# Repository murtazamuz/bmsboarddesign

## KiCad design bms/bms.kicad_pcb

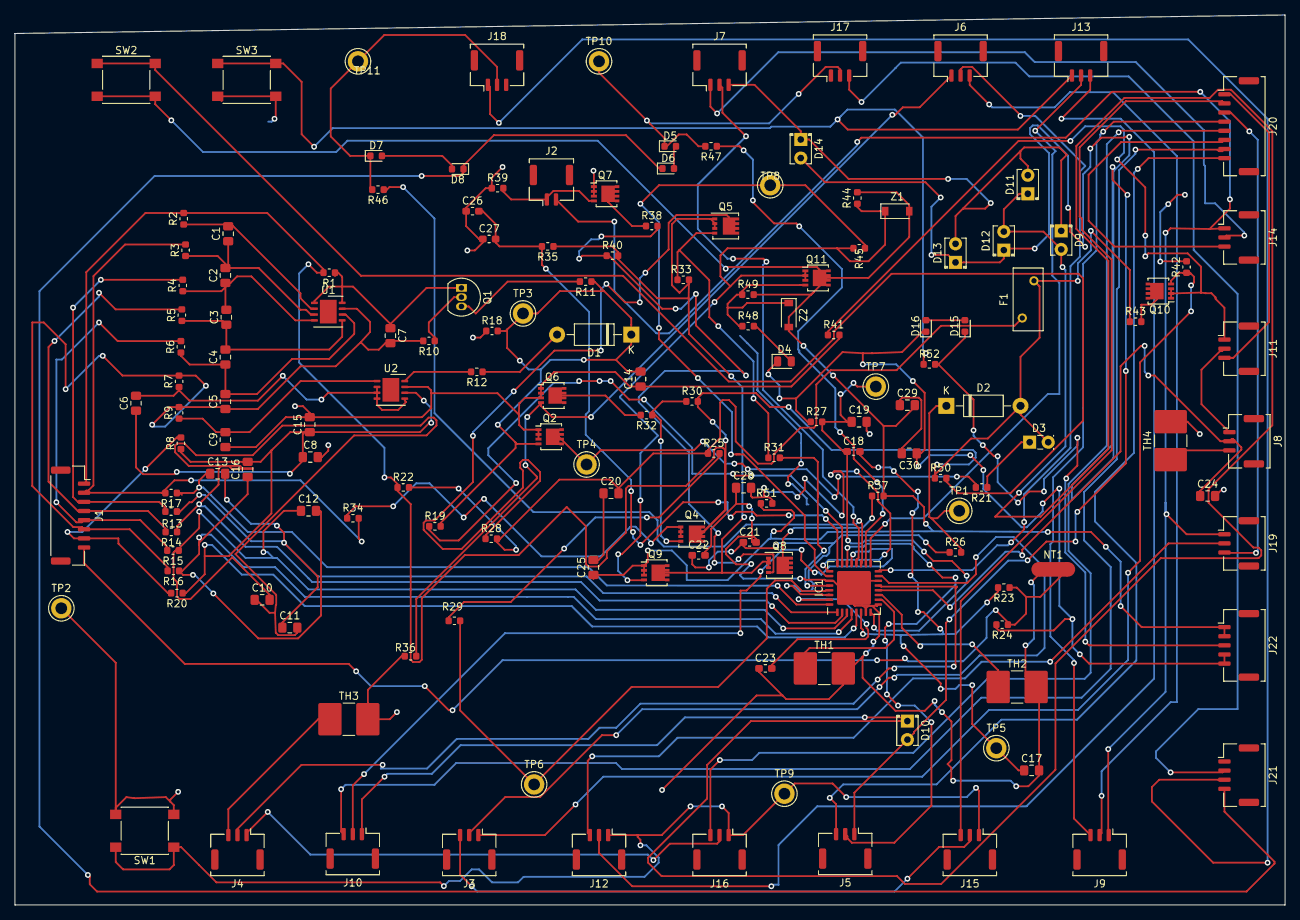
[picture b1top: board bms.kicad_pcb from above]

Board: 2 copper layers, 174.0 x 121.9 mm, 155 parts (0 on the bottom side), 109 nets.

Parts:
C1, C2, C3, C4, C5, C6, C7, C8, C9, C10, C11, C12, C13, C14, C15, C16, C17, C19, C20, C24, C25, C28, C29, C30: 0.1uF; C_0805_2012Metric_Pad1.15x1.40mm_HandSolder
C18, C21, C22, C23, C26, C27: 100pF; C_0603_1608Metric_Pad1.05x0.95mm_HandSolder
D1, D2: 1N5819; D_DO-41_SOD81_P10.16mm_Horizontal
D3: LED; LED_Rectangular_W3.9mm_H1.8mm_FlatTop
D4: DIODE; D_0805_2012Metric
D5, D6, D7, D8, D15, D16: D_Zener_ALT; D_0603_1608Metric
D9, D10, D11, D12, D13, D14: GREEN; LED_D2.0mm_W4.0mm_H2.8mm_FlatTop
F1: 30A fuse; Fuse_BelFuse_0ZRE0008FF_L8.3mm_W3.8mm
IC1: BQ40Z80RSMT; QFN-32-1EP_7x7mm_P0.65mm_EP4.65x4.65mm
J1: Conn_01x08; Molex_CLIK-Mate_502386-0870_1x08-1MP_P1.25mm_Horizontal
J2: Conn_01x02; Molex_CLIK-Mate_502382-0270_1x02-1MP_P1.25mm_Vertical
J3, J4, J5, J6, J7, J8, J9, J10, J11, J12, J13, J14, J15, J16, J17, J18, J19: Conn_01x03; Molex_CLIK-Mate_502382-0370_1x03-1MP_P1.25mm_Vertical
J20: Conn_01x08; Molex_CLIK-Mate_502382-0870_1x08-1MP_P1.25mm_Vertical
J21: Conn_01x04; Molex_CLIK-Mate_502382-0470_1x04-1MP_P1.25mm_Vertical
J22: Conn_01x05; Molex_CLIK-Mate_502382-0570_1x05-1MP_P1.25mm_Vertical
NT1: Net-Tie_2; NetTie-2_SMD_Pad2.0mm
Q1: 2N3905; TO-92_Inline
Q2: BUK7M9R9-60EX; LFPAK33
Q4, Q5, Q8: DMP3013SFV; Diodes_PowerDI3333-8
Q6, Q7, Q9, Q10, Q11: BUK7M12-40EX; LFPAK33
R1, R13, R14, R15, R16, R17, R20, R23, R26, R27, R28, R37, R46, R47: 100; R_0603_1608Metric
R2, R3, R4, R5, R6, R7, R8, R9, R10, R29, R52: 1k; R_0603_1608Metric
R11, R12, R19: 5.1k; R_0603_1608Metric
R18: 20k; R_0603_1608Metric
R21: 1K; R_0603_1608Metric
R22: 0; R_0603_1608Metric
R24: 0.001; R_0603_1608Metric
R25, R30, R32, R33, R36, R38, R39, R40, R42, R44, R48, R49: 10M; R_0603_1608Metric
R31, R50: 10k; R_0603_1608Metric
R34: 200; R_0603_1608Metric
R35: 510; R_0603_1608Metric
R41: 10K; R_0603_1608Metric
R43: 332K; R_0603_1608Metric
R45: 4.02K; R_0603_1608Metric
R51: 1.1k; R_0603_1608Metric
SW1, SW2, SW3: SW_Push_Dual; SW_Push_1P1T_NO_6x6mm_H9.5mm
TH1, TH2, TH3, TH4: Thermistor; R_2816_7142Metric_Pad3.20x4.45mm_HandSolder
TP1, TP2, TP3, TP4, TP5, TP6, TP7, TP8, TP9, TP10, TP11: TestPoint; TestPoint_Keystone_5005-5009_Compact
U1, U2: BQ771807DPJR; DFN-8-1EP_4x4mm_P0.8mm_EP2.3x3.24mm
Z1, Z2: MMSZ5246B-7-F; D_SOD-123

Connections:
6P: J1.2, R3.2, R17.2, R34.2
7P: D2.2, D3.2, F1.2, J1.1, Q4.5, R1.2, R2.2, R22.1, R30.2, R43.1, R50.1
/PACK: C28.2, IC1.25, R51.2
GNDPWR: C30.1, D4.1, D16.1, J22.4, J22.5, R24.2, R27.1
unnamed: C1.1, C2.2, R3.1, U1.3
unnamed: C1.2, R2.1, U1.2
unnamed: C2.1, C3.2, R4.1, U1.4
unnamed: C3.1, C4.2, R5.1, U1.5
unnamed: C4.1, C5.2, R6.1, U1.6
unnamed: C5.1, C7.2, J1.6, R7.2, R9.2, R10.2, R16.2, U1.7
unnamed: C6.2, R7.1, U2.2, U2.3, U2.4, U2.5
unnamed: C7.1, Q1.1, R1.1, U1.1, U1.8
unnamed: C9.2, R9.1, U2.1
unnamed: C10.1, C11.2, IC1.2, R14.1
unnamed: C10.2, C12.1, IC1.3, R15.1
unnamed: C11.1, C13.2, IC1.1, R13.1
unnamed: C12.2, C16.1, IC1.4, R16.1
unnamed: C13.1, IC1.32, R17.1
unnamed: C14.2, D1.1, Q2.4, R11.1, R18.2, R19.2, TP3.1
unnamed: C6.1, C8.1, C15.1, C16.2, IC1.5, R8.1, R20.1, U2.6
unnamed: C17.1, C18.2, IC1.6, R23.2, TP5.1
unnamed: C18.1, C19.1, IC1.8, R27.2, TP7.1
unnamed: C20.1, C25.2
unnamed: C20.2, F1.1, R22.2, R25.1, R28.2
unnamed: C21.1, C22.1, IC1.30, R26.1
unnamed: C23.2, IC1.31
unnamed: C24.1, IC1.12, J8.2
unnamed: C26.2, C27.2, IC1.24, R35.2
unnamed: C29.1, C30.2
unnamed: D1.2, R12.1
unnamed: D2.1, R26.2, TP1.1
unnamed: D3.1, R21.1
unnamed: D4.2, R48.2
unnamed: D5.1, J17.2, R47.2, TP10.1
unnamed: D5.2, D6.2
unnamed: D6.1, D8.1, J21.4
unnamed: D7.1, J18.2, R46.2, TP11.1
unnamed: D7.2, D8.2
unnamed: D9.2, D10.1, D11.1, D12.2, J10.1
unnamed: D10.2, D12.1, D13.1, D14.2, J5.1
unnamed: D9.1, D11.2, D13.2, D14.1, J7.3
unnamed: D15.1, J22.3, R52.2
unnamed: D15.2, D16.2
unnamed: IC1.10, TH1.1
unnamed: IC1.11, TH2.1
unnamed: IC1.13, J4.2
unnamed: IC1.15, J3.2
unnamed: IC1.16, J6.2
unnamed: IC1.17, J13.2
unnamed: IC1.18, R47.1
unnamed: IC1.19, R46.1
unnamed: IC1.20, J7.2
unnamed: IC1.21, J10.2
unnamed: IC1.22, J5.2
unnamed: IC1.23, R19.1
unnamed: IC1.26, R45.1, TP8.1
unnamed: IC1.28, R31.2
unnamed: IC1.29, R29.2, TP6.1
unnamed: J1.3, R4.2, R13.2
unnamed: J1.4, R5.2, R14.2
unnamed: J1.5, R6.2, R15.2
unnamed: J1.7, R8.2, R20.2
unnamed: J1.8, NT1.2, R23.1, R24.1
unnamed: J2.1, Q7.4, R39.2
unnamed: J3.1, Q10.4, R42.1
unnamed: J4.3, TH3.1
unnamed: J6.1, Q6.4, R36.2
unnamed: J6.3, J9.2
unnamed: J8.3, TH4.1
unnamed: J10.3, J20.7
unnamed: J11.1, Q10.1, Q10.2, Q10.3, R41.1
unnamed: J8.1, J11.2
unnamed: J11.3, J20.1
unnamed: J12.1, J15.1, J16.1, SW1.1, TP9.1
unnamed: J12.2, J13.3
unnamed: J12.3, J19.2
unnamed: J2.2, J9.1, J14.1, J19.1
unnamed: J7.1, J14.2
unnamed: J14.3, J20.6
unnamed: J3.3, J15.2
unnamed: J15.3, J20.2
unnamed: J4.1, J16.2
unnamed: J16.3, J20.5
unnamed: J17.3, J21.2
unnamed: J18.1, J21.3
unnamed: J19.3, J20.3
unnamed: J9.3, J20.4
unnamed: J5.3, J20.8
unnamed: Q1.2, R10.1
unnamed: Q1.3, R11.2
unnamed: Q2.5, R21.2, TP4.1
unnamed: R25.2, R29.1
unnamed: Q5.1, Q5.2, Q5.3, Q8.1, Q8.2, Q8.3, Q9.5, R33.2, R35.1, R40.2
unnamed: Q4.1, Q4.2, Q4.3, R34.1
unnamed: Q4.4, R30.1, R32.1
unnamed: Q5.4, R31.1, R33.1
unnamed: Q5.5, R28.1
unnamed: Q6.5, R32.2
unnamed: Q7.5, R38.1
unnamed: Q8.4, R38.2, R40.1
unnamed: Q8.5, R37.1
unnamed: Q10.5, R43.2
unnamed: Q9.4, Q11.1, Q11.2, Q11.3, R44.1, R45.2, Z1.1
unnamed: Q11.4, R48.1, R49.1, Z2.1
unnamed: R12.2, U2.8
unnamed: R50.2, SW2.1
PACK+: C25.1, C29.2, J22.1, J22.2, Q9.1, Q9.2, Q9.3, Q11.5, R37.2, R44.2, R49.2, R51.1, SW2.2, Z1.2, Z2.2
PRES_SHUTDOWN: J13.1, R52.1, SW3.1
VSS: C8.2, C9.1, C14.1, C15.2, C17.2, C19.2, C21.2, C22.2, C23.1, C24.2, C26.1, C27.1, C28.1, IC1.7, IC1.9, IC1.14, IC1.27, IC1.33, NT1.1, Q2.1, Q2.2, Q2.3, Q6.1, Q6.2, Q6.3, Q7.1, Q7.2, Q7.3, R18.1, R36.1, R39.1, R41.2, R42.2, SW1.2, SW3.2, TH1.2, TH2.2, TH3.2, TH4.2, TP2.1, U2.7
